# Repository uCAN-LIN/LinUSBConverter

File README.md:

# USB LIN Converter (uLC)

> **Open source USB ↔ LIN bus dongle. LIN 2.1 master, slave or monitor. SLCAN-compatible virtual COM port - works on Windows, Linux and macOS with no proprietary drivers.**

The **USB LIN Converter (uLC)** is a small open-source USB dongle (STM32F042, ~31 × 18 mm) that lets a PC act as a LIN bus master, slave or passive monitor. It enumerates as a USB CDC virtual COM port and speaks an SLCAN-style ASCII protocol, so it bridges into Linux SocketCAN via `slcand` and works with parts of can-utils.

A commercial automotive LIN analyzer typically costs hundreds to thousands of euros. This one is around **$27** on [Tindie](https://www.tindie.com/products/lll7/usb-lin-converter/).

The LIN protocol implementation is based on [openLIN](https://github.com/open-LIN).

---

## Features

- LIN 2.1 support
- **Monitor mode** - full frame reception plus single-frame transmission
- **Master mode** - up to 16 scheduled frame slots
- **Slave mode** - up to 16 scheduled frame slots for slave simulation
- 9600 / 19200 baud rate selection
- **Optical isolation** between LIN and the USB / PC side
- Software-controlled termination resistors
- External 4.5 - 28 V powers the LIN transceiver
- Device size 31 × 18 mm (without USB connector)
- USB DFU bootloader for firmware updates
- No proprietary drivers - Linux / macOS / Windows
- **MCP server** so AI agents can sniff and reverse-engineer a LIN bus ([see below](#ai-agents-mcp-server))

---

## Where to buy

| Where | Region | Link |
|---|---|---|
| **Tindie** | Worldwide | https://www.tindie.com/products/lll7/usb-lin-converter/ |
| **Lectronz** | EU | https://lectronz.com/stores/ucandevices |
| **Elty** | Poland / EU | https://elty.pl/ |
| **Kamami** | Poland / EU | https://kamami.pl/ |

---

## Quickstart

1. Plug the device into a USB port. It enumerates as a virtual COM port (`COM3` on Windows, `/dev/ttyACM0` on Linux, `/dev/cu.usbmodem*` on macOS).
2. No driver is needed on Windows 10/11, Linux or macOS: the built-in USB CDC driver is used. Since firmware 3.5 the device has its own USB ID from [pid.codes](https://pid.codes/1209/2779/), `1209:2779`; older firmware used ST's generic `0483:5740` (on Windows 7/8 that needs the [ST Virtual COM Port driver](https://www.st.com/en/development-tools/stsw-stm32102.html)).
3. Open the port at any baud rate (USB CDC ignores baud). Line ending must be CR (`0x0D`).
4. Power the LIN side with 4.5 - 28 V on the external supply pin.
5. Send `S0` to select 19200 baud, then `l` to enter monitor mode. Bus traffic will start to appear.

### Linux SocketCAN bridge

```bash
sudo slcand -o -s8 -t hw -S 921600 /dev/ttyACM0 slcan0
sudo ip link set slcan0 up
candump slcan0
```

### Python (pyserial) sniff snippet

```python
import serial
ser = serial.Serial('/dev/ttyACM0', timeout=1)
ser.write(b'S0\r')   # 19200 baud
ser.write(b'l\r')    # monitor mode
while True:
    line = ser.readline()
    if line:
        print(line.decode(errors='replace').strip())
```

A higher-level Python library is provided in [`python_lib/`](python_lib/) (package `ucanlintools`).

### AI agents (MCP server)

[`python_lib/ucanlintools/mcp_server.py`](python_lib/ucanlintools/mcp_server.py) is an
MCP server that lets an AI agent sniff and reverse-engineer a LIN bus: capture traffic
with per-id periods and changing bits, log every data change while you press a button,
find the bus speed and checksum type automatically, and decode or encode signals from
an LDF file. It is **read-only by default**; sending frames and acting as master or
slave needs `--allow-transmit`.

```bash
uvx ucan-lin-mcp --mock             # from PyPI, no install step (Python 3.10+)
# or from this repo: pip install -e "python_lib[mcp]" && ucanlin-mcp --mock
```

Register it with any MCP client as a stdio server:

```json
{
  "mcpServers": {
    "lin": {"command": "uvx", "args": ["ucan-lin-mcp", "--port", "COM3"]}
  }
}
```

`--mock` runs a simulated bus. [`mcp_package/`](mcp_package/) is the `ucan-lin-mcp` launcher
package and [`server.json`](server.json) its MCP Registry entry.

Tools: `device_info`, `monitor_bus`, `detect_bus`, `load_ldf`, `decode_frame`,
`encode_frame`, and with `--allow-transmit` also `send_frame`, `run_master`, `run_slave`.

---

## ASCII command reference

All commands are ASCII terminated with CR (`0x0D`). Errors return `0x07` (BEL).

| Command | Description |
|---|---|
| `O` | Open in master mode |
| `L` | Open in slave mode |
| `l` | Open in monitor mode |
| `C` | Close LIN port |
| `Sx` | Baud: `S2` = 9600, others = 19200 |
| `V` / `v` / `N` | Hardware / firmware version / serial number query |
| `tiiildd...` | Transmit full header + data frame (id, length, data) |
| `r0iil` | Header only request (slave answers) |
| `r1ff0` | Master mode: start sending frames from schedule table |
| `r2ff0` | Clear schedule table |
| `r31` / `r30` | Checksum for all frames: `r31` classic (LIN 1.x), `r30` enhanced (LIN 2.x, default). Diagnostic frames 0x3C/0x3D always use classic. Replies `Z`. Kept until power off; `t31`/`t30` work too. |
| `t04bbbb` | Custom LIN baud rate, `bbbb` = 4 hex digits (e.g. `t0428B1` = 10417 baud). Send before adding frames. Replies `Z`. |
| `T0iipptt0ldd...` / `R0iipptt0l` | Frame with explicit delay `pp` and response wait time `tt` (ms, hex), e.g. `T00A643001A5`. `pp` is the time from the start of the previous slot's header to this slot's header (firmware 3.4 and later; older firmware started it when the previous frame ended). |
| | Commands are executed one at a time: wait for the reply (CR, `z`/`Z` or BEL) before sending the next one. |

Full command reference and examples: https://ucandevices.github.io/ulc.html

---

## Repository layout

| Directory | Contents |
|---|---|
| [`embedded/`](embedded/) | STM32F042 firmware sources (STM32CubeMX project `LUCEmbedded.ioc`, Atollic TrueSTUDIO project under `embedded/TrueSTUDIO/`). USB layer generated with STM32CubeMX. |
| [`pcb/`](pcb/) | Open-hardware KiCad project for the LIN_USB_CONVERTER board, Gerbers and 1-click BOM. |
| [`python_lib/`](python_lib/) | `ucanlintools` Python package with high-level master / slave / monitor helpers and examples. |
| [`doc/`](doc/) | LIN 2.2A specification, MCU datasheet, LIN transceiver datasheet and supporting documents. |

---

## Build

Source is pure C. Import the Eclipse project in `embedded/TrueSTUDIO/LUCEmbedded` into **STM32CubeIDE** (tested with 1.19) and build the `Debug` configuration; the image is `Debug/LUCEmbedded.bin`. The openLIN stack is vendored in `embedded/Src` (`open_lin_*.c/h`, `implementation/ST32`). The USB CDC layer was generated with STM32CubeMX from `embedded/LUCEmbedded.ioc`.

## Bootloader

The STM32F042 has an embedded ROM USB DFU bootloader. To enter it from a running device send `boot\r` over the virtual COM port. See this [tutorial](https://www.youtube.com/watch?v=-gnX25AGyI0) for the flashing flow.

With STM32CubeProgrammer installed, the flashing can be scripted:

```bash
python -c "import serial; serial.Serial('COM3').write(b'boot\r')"
STM32_Programmer_CLI -c port=usb1 -w LUC_0308.bin 0x08000000 -v -g 0x08000000
```

---

## Testing

The test suite lives in [`python_lib/tests`](python_lib/tests) (pytest). It covers the firmware and the `ucanlintools` library:

| File | Hardware | What it tests |
|---|---|---|
| `test_ldf_parser.py`, `test_linframe.py`, `test_luc_encoding.py` | none | LDF parsing, signal encode/decode, frame formatting |
| `test_luc_hardware.py` | 1-2 dongles | Library: version query, mode switching, monitor loopback, master → slave |
| `test_firmware_protocol.py` | 1-2 dongles | Firmware over raw serial: malformed-command rejection, 16-row table limit, all frame lengths 1-8 in both directions with exact data check, live data update, diagnostic frames 0x3C/0x3D, unanswered headers, extended `T`/`R` row timing, custom baud rate, monitor reception (including back-to-back frames) and monitor transmit. Parametrized for 19200 and 9600 baud. |
| `test_lib_simulation.py` | 2 dongles | Scripted `MasterSimulation.py` / `SlaveSimulation.py`: LDF-encoded master frame, slave response, both changing at runtime, at both speeds |

**Setup:** two converters on one LIN bus (LIN pins connected, external LIN supply applied). `LUC_MASTER_PORT` is used as LIN master, `LUC_SLAVE_PORT` as slave / monitor. Tests skip automatically when a port can't be opened, so the offline tests always run.

```bash
cd python_lib
pip install pyserial lark pytest
LUC_MASTER_PORT=COM3 LUC_SLAVE_PORT=COM56 PYTHONPATH=. pytest tests -v
# swap the ports and run again to test each converter in both roles
LUC_MASTER_PORT=COM56 LUC_SLAVE_PORT=COM3 PYTHONPATH=. pytest tests -v
```

On Windows PowerShell set the variables with `$env:LUC_MASTER_PORT="COM3"` etc.

### How firmware 3.8 was tested

- Same setup, both converters flashed with `LUC_0308.bin`.
- Monitor fix: frames sent back to back (each one as soon as the previous command was acknowledged, about 4 ms apart at 19200 baud) leave less idle time than the monitor's end-of-frame timeout, so the next break reset the reception and the previous frame was lost. The monitor now reports the previous frame when the next break arrives. Before: 15 of 32 frames received; with the fix: 32 of 32, in order.
- New regression test `test_monitor_reports_back_to_back_frames` (fails on 3.7, passes on 3.8); full suite run twice with the roles swapped: **66/66 passed** in each direction.
- CANgaroo uLC driver hardware test (two converters, Windows): 32/32 checks passed.

### How firmware 3.7 was tested

- Same setup, both converters flashed with `LUC_0307.bin`.
- Slave fix traced byte by byte with a diagnostic build: when the slave subscribed a frame nobody answered, the next header's break byte was counted as that frame's data, and the stale count made the slave take the following frame's last data byte as its checksum and drop it. With the fix the slave receives every following frame (23 of 23 in 1.5 s, before 0).
- New regression test `test_slave_subscribed_to_unanswered_header_keeps_next_frame`; full suite run twice with the roles swapped: **65/65 passed** in each direction.

### How firmware 3.6 was tested

- Same setup, both converters flashed with `LUC_0306.bin`.
- Clock recovery checked with a test-only build that reported the CRS registers: the CRS synchronised to the USB SOF within the first seconds (SYNCOK set, no errors afterwards) and moved the HSI48 trim from 32 to 35 on one converter, i.e. that converter's clock ran measurably slow without it.
- Full suite run twice with the roles swapped: **63/63 passed** in each direction; master slot periods unchanged from 3.4 (within about 1 ms of the configured delay).

### How firmware 3.5 was tested

- Same setup, both converters flashed with `LUC_0305.bin`. They enumerate as `1209:2779` and Windows 10 loads its built-in CDC driver without any installation.
- Full suite run twice with the roles swapped: **55/55 passed** in each direction. Firmware 3.5 changes only the USB ID, the LIN code is the same as 3.4.

### How firmware 3.4 was tested

- Two uLC converters (hardware `V0001`), both flashed with `LUC_0304.bin`, connected on one powered LIN bus.
- Full suite run twice with the roles swapped: **55/55 passed** in each direction (110 test runs).
- Master slot timing measured with the second converter as monitor (3 s window, 19200 baud): the slot period now matches the configured delay within about 1 ms for 0, 2, 4 and 8 data bytes, for 10, 20 and 40 ms delays, and for unanswered subscriber slots. Firmware 3.3 added the frame time to every slot (+2 to +6 ms) and the full response timeout to unanswered subscriber slots (+12 ms).

### How firmware 3.3 was tested

- Two uLC converters (hardware `V0001`), both flashed with `LUC_0303.bin`, connected on one powered LIN bus.
- Full suite run twice with the roles swapped: **47/47 passed** in each direction (94 test runs).
- Bus throughput measured during testing (4 s window, 16-frame schedule): every frame scheduled 12-14 times at 19200 baud and 10-11 times at 9600 baud, no lost or corrupted frames, no unexpected serial output.
- The bugs fixed in 3.3 each have a regression test: malformed row locking the table, slave mode stalling after the first response at 9600 baud, slave mode not answering at all, master not reporting slave responses, 6-8 byte responses timing out at 9600 baud, and the classic checksum setting being ignored. The checksum tests were also run against the previous firmware and fail there, as expected.

---

## FAQ

**What is the cheapest USB LIN bus converter that works on Linux?**
The uCanDevices USB LIN Converter (uLC) is an open source dongle around $27 that enumerates as a USB CDC virtual COM port on Linux, macOS and Windows. It uses an SLCAN-style ASCII protocol so it bridges into SocketCAN via `slcand`.

**Does it support master and slave mode?**
Yes - monitor (full reception plus single-frame transmission), master (up to 16 scheduled slots) and slave (up to 16 slots for slave simulation). Modes are selected with the `O`, `L` and `l` commands.

**Is the LIN side optically isolated from the USB host?**
Yes. The LIN transceiver is optically isolated from the PC side, protecting the host from automotive transients. The LIN side needs an external 4.5 - 28 V supply since USB only powers the MCU.

**Which LIN baud rates and LIN version are supported?**
LIN 2.1, with selectable 9600 and 19200 baud. Classic and enhanced checksum are switchable with the `r31` / `r30` commands (firmware 3.3 and later). Custom frame timing is supported in master mode.

**Can I use it to flash an ECU over LIN?**
It is a generic LIN interface. ECU flashing depends entirely on the target ECU's own LIN bootloader; if that bootloader is documented or already supported by an existing tool, you can drive it through this dongle.

**Is the firmware open source?**
Yes - this repository contains firmware (`embedded/`), hardware (`pcb/`) and the Python helper library (`python_lib/`). The device also has a USB DFU bootloader for in-field updates.

---

## Related projects

- LIN protocol implementation: [openLIN](https://github.com/open-LIN)
- Sibling products: [USB CAN Converter (UCCB)](https://ucandevices.github.io/uccb.html), [CAN FD USB Converter (CFUC)](https://ucandevices.github.io/cfuc.html), [SENT (J2716) USB Converter](https://ucandevices.github.io/sentusb.html)

## Links

- Product page: https://ucandevices.github.io/ulc.html
- All uCanDevices products: https://ucandevices.github.io/
- Contact: devices.ucan@gmail.com

## License

See [LICENSE](LICENSE).

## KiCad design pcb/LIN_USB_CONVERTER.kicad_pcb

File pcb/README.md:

Printed circuit board for LinUSBConverter. Project is made in KiCad.

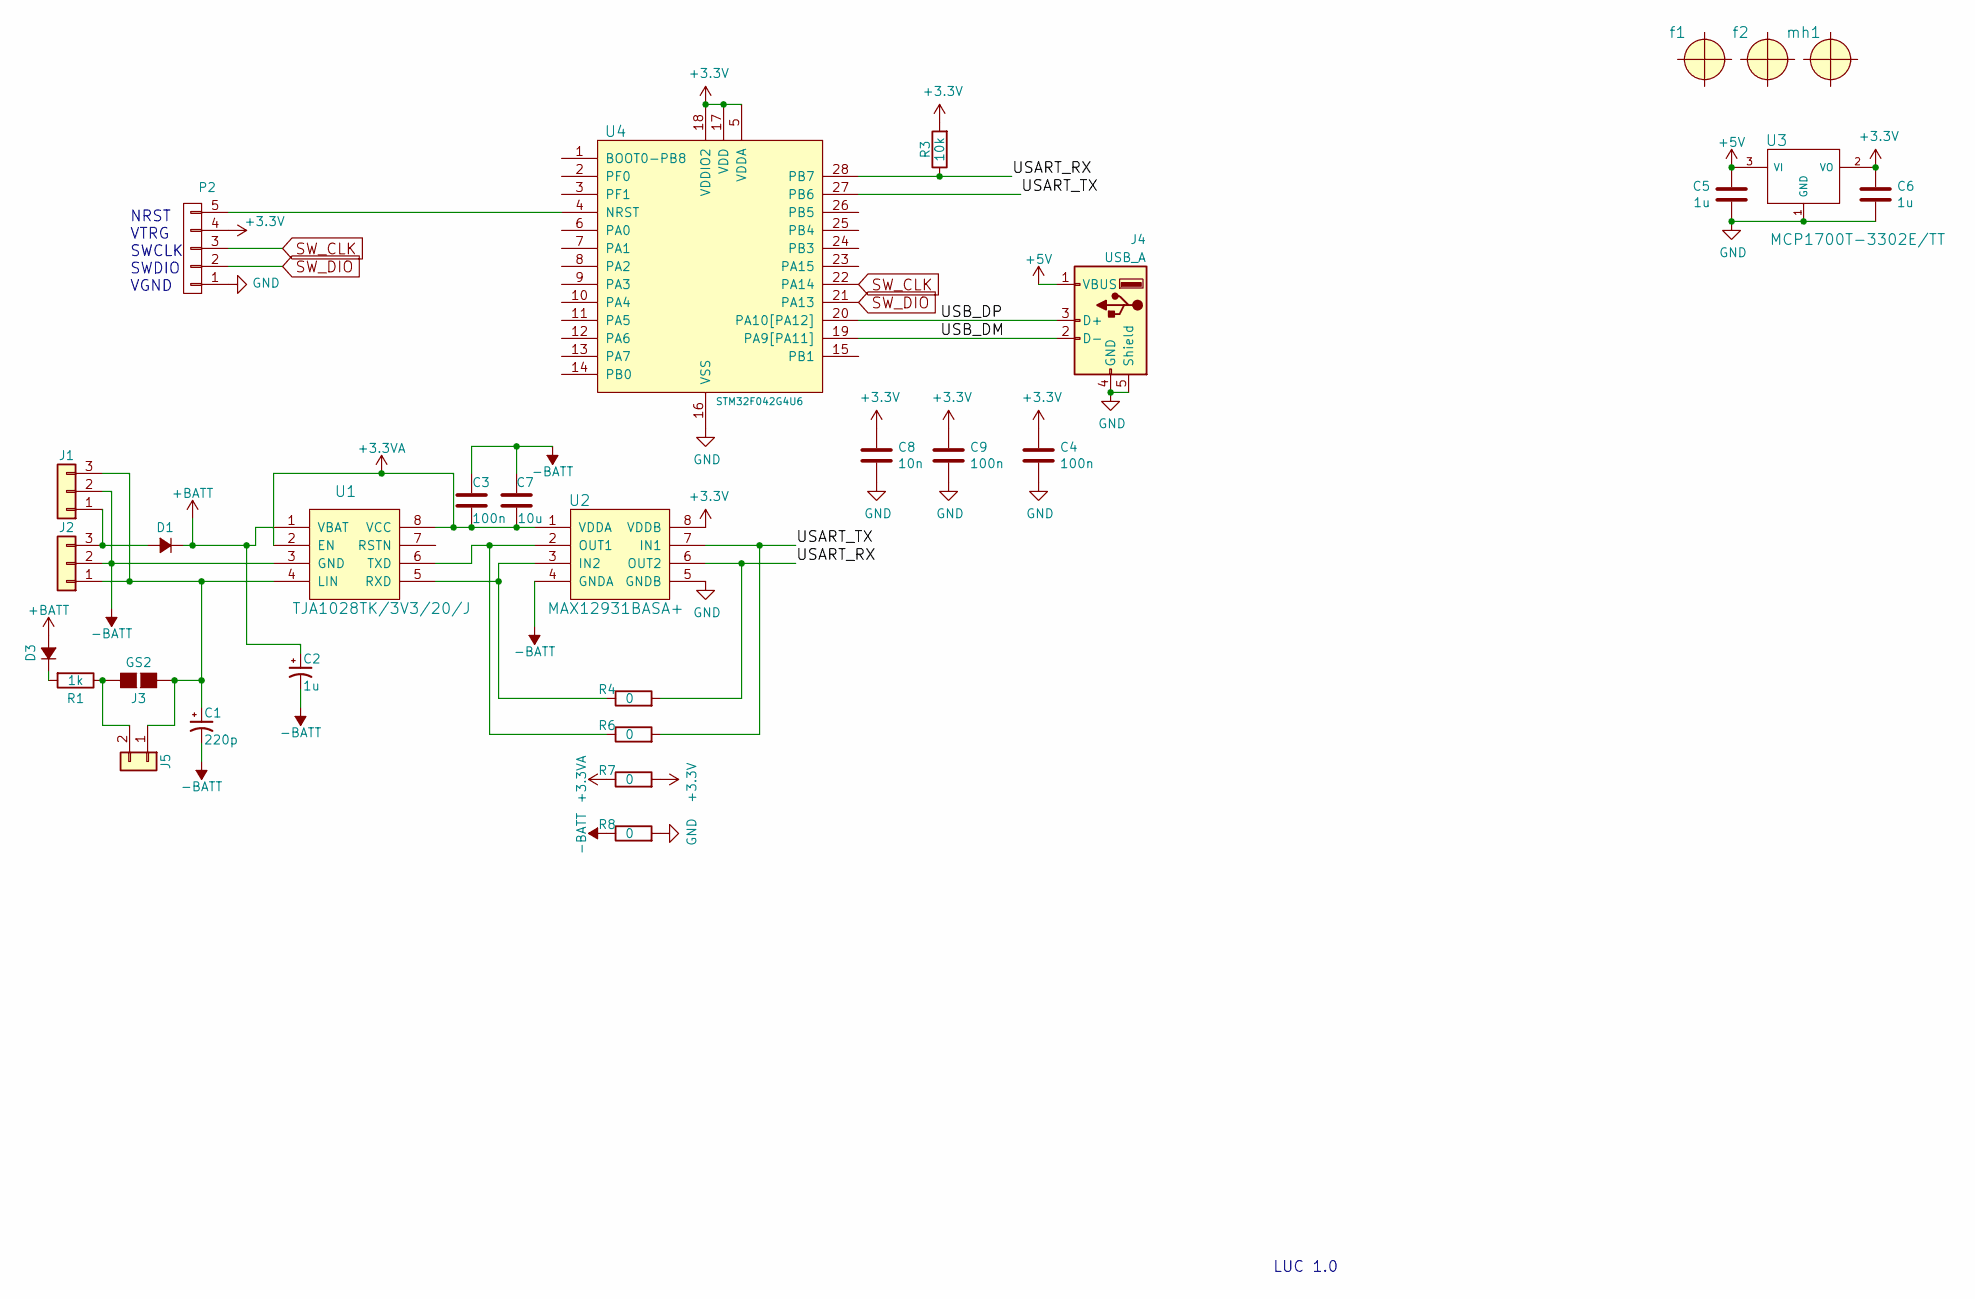
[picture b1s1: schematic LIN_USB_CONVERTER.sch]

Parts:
C1: 220p; C_0603
C2: 1u; C_0805
C3, C4, C9: 100n; C_0603
C5, C6: 1u; C_0603
C7: 10u; C_0805
C8: 10n; C_0603
D1, D3: SMBD914E6327HTSA1; D_SOT-23_ANK
J1: Conn_01x03; Pin_Header_Straight_1x03_Pitch2.54mm
J2: TerminalBlock; TerminalBlock_Altech_AK300-3_P5.00mm
J3: GS2
J4: USB_A; USB_A_DS1097R
J5: Conn_01x02; Pin_Header_Straight_1x02_Pitch2.54mm
P2: CONN_01X05; swd_smd_conn5
R1: 1k; R_0603
R3: 10k; R_0603
R4, R6, R7, R8: 0; R_0603
U1: TJA1028TK/3V3/20/J; SOIC-8_3.9x4.9mm_Pitch1.27mm
U2: MAX12931BASA+; SOIC-8-N_MAXIM
U3: MCP1700T-3302E/TT; SOT-23
U4: STM32F042G4U6; ST_UFQFPN-28_3x3mm_P0.5mm; MFG Part Num STM32F042G4U6
f1, f2: fiducial; Fiducial_1mm_Dia_2.54mm_Outer_CopperTop
mh1: fiducial; 1pin

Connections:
+3.3VA: C3.2, C7.2, R7.1, U1.2 (EN), U1.8 (VCC), U2.1 (VDDA)
+3V3: C4.1, C6.1, C8.1, C9.1, P2.4, R3.2, R7.2, U2.8 (VDDB), U3.2 (VO), U4.5 (VDDA), U4.17 (VDD), U4.18 (VDDIO2)
+5V: C5.1, J4.1 (VBUS), U3.3 (VI)
+BATT: C2.1, D1.1 (K), D3.2 (A), U1.1 (VBAT)
-BATT: C1.2, C2.2, C3.1, C7.1, J1.2, J2.2, R8.1, U1.3 (GND), U2.4 (GNDA)
/USART_RX: R3.1, R4.2, U2.6 (OUT2), U4.28 (PB7)
/USART_TX: R6.2, U2.7 (IN1), U4.27 (PB6)
/USB_DM: J4.2 (D-), U4.19 (PA9[PA11])
/USB_DP: J4.3 (D+), U4.20 (PA10[PA12])
GND: C4.2, C5.2, C6.2, C8.2, C9.2, J4.4 (GND), J4.5 (Shield), P2.1, R8.2, U2.5 (GNDB), U3.1 (GND), U4.16 (VSS)
unnamed: C1.1, J1.3, J2.1, J3.1 (G1), J5.1, U1.4 (LIN)
unnamed: D1.2 (A), J1.1, J2.3
unnamed: D3.1 (K), R1.2
unnamed: J3.2 (G2), J5.2, R1.1
unnamed: P2.5, U4.4 (NRST)
unnamed: R4.1, U1.5 (RXD), U2.3 (IN2)
unnamed: R6.1, U1.6 (TXD), U2.2 (OUT1)
SW_CLK: P2.3, U4.22 (PA14)
SW_DIO: P2.2, U4.21 (PA13)

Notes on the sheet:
NRST VTRG SWCLK SWDIO VGND
LUC 1.0

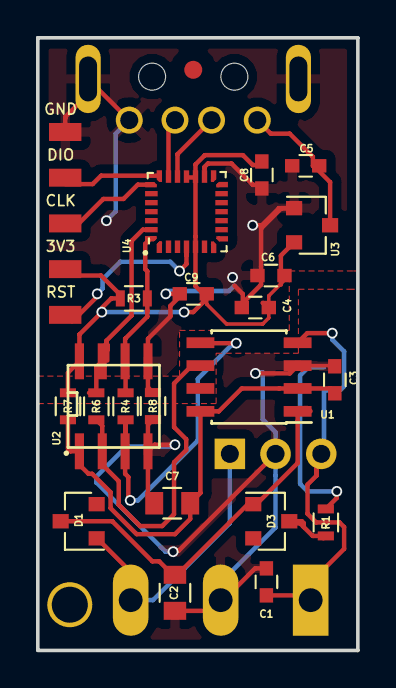
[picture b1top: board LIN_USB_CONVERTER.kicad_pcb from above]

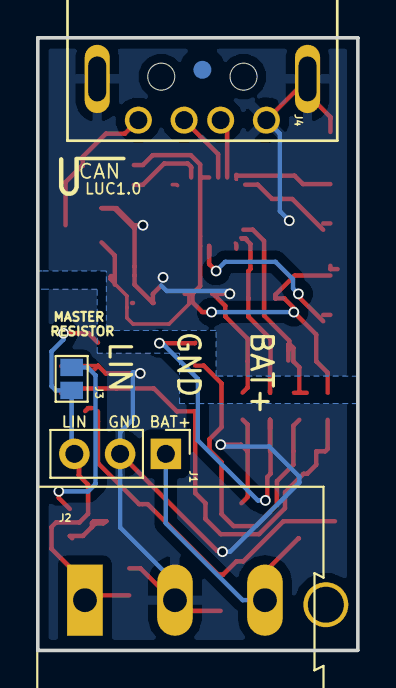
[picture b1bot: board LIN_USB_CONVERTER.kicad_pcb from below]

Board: 2 copper layers, 17.8 x 34.0 mm, 29 parts (5 on the bottom side), 19 nets.

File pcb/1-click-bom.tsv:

References	Qty	Description
C1	1	CP1 Small 220p Polarised capacitor C 0603
C2	1	CP1 Small 1u Polarised capacitor C 0603
C8	1	C 10n Unpolarized capacitor 0402
C9, C5, C6, C3, C4	5	C 100n Unpolarized capacitor 0402
D1, D3	2	D Small ALT SMBD914E6327HTSA1 Diode, small symbol, alternativ symbol SOT-23 ANK
D2	1	D Schottky Small ALT 1N5819HW-7-F diode, small symbol, alternativ symbol SOD-123
J1	1	Conn 01x03 Generic connector, single row, Pin Header Straight 1x03 Pitch2.54mm
J2	1	Conn 01x03 Generic connector, single row, TerminalBlock Altech AK300-3 P5.00mm
J3	1	GS2 2-pin jumper/solder bridge
J4	1	USB A Type connector DS1097R
J5	1	Conn 01x02 Generic connector, single row, Pin Header Straight 1x02 Pitch2.54mm
P2	1	CONN 01X05 swd smd conn5
R1	1	R 1k Resistor 0603
R2	1	R 50 Resistor 0603
R5, R3	2	R 10k Resistor 0603
R6, R4, R7, R8	4	R 0 Resistor 0603
U1	1	TJA1028 HVSON8
U2	1	MAX12931 SOIC-8-N
U3	1	MCP1700T-3302E/TT SOT-23
U4	1	STM32F042C6T6 STM32F042G4U6 UFQFPN 28
f1, f2	2	fiducial Fiducial 1mm Dia 2.54mm Outer CopperTop
mh1	1	fiducial 1pin

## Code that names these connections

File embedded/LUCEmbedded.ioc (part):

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Mcu.Name=STM32F042G(4-6)Ux
Mcu.Package=UFQFPN28
Mcu.UserName=STM32F042G4Ux
PA11.Mode=Device
PA11.Signal=USB_DM
PA12.Mode=Device
PA12.Signal=USB_DP
PA13.Mode=Serial_Wire
PA13.Signal=SYS_SWDIO
PA14.Mode=Serial_Wire
PA14.Signal=SYS_SWCLK
PB6.Mode=LIN
PB6.Signal=USART1_TX
PB7.Mode=LIN
PB7.Signal=USART1_RX
RCC.SYSCLKFreq_VALUE=48000000
RCC.SYSCLKSource=RCC_SYSCLKSOURCE_HSI48
board=LUCEmbedded

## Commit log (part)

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2018-02-10 Init
2018-02-13 Open lin implmentation to ST
2018-02-13 Add Open_Lin as submodule
2018-02-14 KiCad project rename
2018-02-14 doc update
2018-03-07 Kicad update
2018-03-07 GitIgnore
2018-03-14 frame reception fixes
2018-03-15 boot add
2018-03-17 Naming update
2018-04-03 PCB release
2018-04-06 Readme update
2018-04-19 GNU License add
2018-04-23 Headers rx fix
2018-05-07 Remove of galvanic spearator
2018-05-25 TJA package update
2018-05-26 Panels add
2018-05-28 Usb holes update
2018-08-14 Rest fix
2018-11-06 LIN monitor rx fix
2019-03-07 Update build configuration
2019-03-09 Cleanup + add Delay, LS HS configuraiton
2019-03-09 Bugfixing for upper case
2019-03-16 Add slave support + python lib draft
2019-03-18 Python lib draft add
2019-03-29 Update close
2019-04-16 Update Low Speed + Serial Number
2019-04-17 LDF parser draft
2019-04-18 Parser update
2019-04-20 Add low speed example
2019-04-23 encode draft
2019-04-26 Exmpale draft
2019-04-27 Add rx handlers
2019-04-27 minor fix
2019-04-30 Release draft
2019-04-30 Release update
2019-05-04 Add examples
2019-06-05 Monitor for 0x3d fix
2019-06-05 8byte long diag cheksum fix
2019-08-05 Selectable baudrate addition
2019-08-05 2.0 release
2020-01-16 Init / Delay uart
2020-01-18 Add USART
2020-01-31 Working proto
2020-03-26 Checksum selection x1/x2
2020-04-15 Diag messagining fix + checksum selection change
2020-07-31 Log update
2021-04-07 fix type and reformat file to be compatible with PEP8
2021-06-14 remove submodule + compile updates
2021-07-16 gitmodules update
2021-07-16 Fix diagnotic_slot
2021-12-14 Fix submodules
2021-12-14 fix for error of type missmach
2022-08-24 added timeout and baudrate as optional settings
2022-08-24 added isRunning function and example usage
2026-06-15 Update python lib
